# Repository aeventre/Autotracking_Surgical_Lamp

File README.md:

# AutoTracking Surgical Robot lamp

## Table of Contents
- [AutoTracking Surgical Robot lamp](#autotracking-surgical-robot-lamp)
  - [Table of Contents](#table-of-contents)
  - [Overview](#overview)
  - [Background](#background)
  - [Acknowledgments](#acknowledgments)
- [System Overview](#system-overview)
- [Software Design](#software-design)
  - [Setup](#setup)
  - [Package Overview](#package-overview)
    - [`command_manager`](#command_manager)
    - [`lamp_gui`](#lamp_gui)
    - [`remote_tracker`](#remote_tracker)
    - [`camera_calibration`](#camera_calibration)
    - [`goal_pose_executor`](#goal_pose_executor)
    - [`controller_coms`](#controller_coms)
    - [`surg_bot_description`](#surg_bot_description)
    - [`surg_bot_moveit_config`](#surg_bot_moveit_config)
  - [Launch Configurations](#launch-configurations)
- [Electrical Design](#electrical-design)
- [CAD](#cad)
  - [3D Printed Components of Surgical Robot](#3d-printed-components-of-surgical-robot)
  - [Sensors and Servos](#sensors-and-servos)
  - [Bill of materials for Surgical Robot](#bill-of-materials-for-surgical-robot)
  - [Bill of Materials for Surgical Robot Base](#bill-of-materials-for-surgical-robot-base)

## Overview
An open-source ROS 2 and MoveIt 2 surgical lamp capable of autonomous real-time tracking of a handheld remote using monocular vision and 3D pose estimation. 

## Background
This project aims to develop a solution to the challenges posed by modern surgical lamps,
particularly focused on the ceiling-mounted lamps. The proposed solution is a responsive
surgical lamp that uses real-time tracking and automated movement to adjust its lighting
position. This approach minimizes manual interaction, reduces delays and allows support staff
to remain focused on higher priority clinical responsibilities

# System Overview

# Software Design

This ROS 2 workspace contains all packages required for the Auto-Tracking Surgical Lamp system. The lamp uses 3D pose tracking of a handheld remote (via green ball detection) to plan and execute motions in real-time, with fallback modes for manual GUI control and demo sequences. The system is built using ROS 2 Jazzy and MoveIt 2.

## Setup

To build and source the workspace:

```bash
cd /path/to/ros2_ws
source /opt/ros/jazzy/setup.bash
rosdep install --from-paths src --ignore-src -r -y
colcon build
source install/setup.bash
```

## Package Overview

### `command_manager`

Manages the system's behavior based on user input. It switches between modes such as idle, manual control, tracking, zeroing, and demo.

**Subscriptions**
- `/system_mode` (`std_msgs/Int32`)
- `/remote_pose` (`geometry_msgs/PoseStamped`)
- `/remote_orientation` (`geometry_msgs/QuaternionStamped`)
- `/user_command` (`surg_lamp_msgs/UserCommand`)

**Publications**
- `/goal_pose` (`geometry_msgs/PoseStamped`)
- `/joint_commands` (`std_msgs/Float64MultiArray`)
- `/user_command` (`surg_lamp_msgs/UserCommand`)

---

### `lamp_gui`

PyQt5-based graphical user interface for interacting with the lamp.

**Features**
- Dropdown menu for system mode selection
- Sliders for manual joint control
- Buttons for triggering demo modes or resets
- Status label for system feedback

**Publications**
- `/system_mode` (`std_msgs/Int32`)
- `/joint_commands` (`std_msgs/Float64MultiArray`)
- `/user_command` (`surg_lamp_msgs/UserCommand`)

---

### `remote_tracker`

Tracks a green marker (ball) on a handheld remote using OpenCV and depth cameras. Estimates the 3D position and uses IMU orientation to compute the full pose.

**Inputs**
- RGB and depth images from stereo cameras
- Camera extrinsics from `camera_calibration`
- IMU orientation from the remote

**Outputs**
- `/remote_pose` (`geometry_msgs/PoseStamped`)
- `/remote_orientation` (`geometry_msgs/QuaternionStamped`)

---

### `camera_calibration`

Contains stereo camera calibration and extrinsic transform files.

**Contents**
- `camera_01.yaml`, `camera_02.yaml`: intrinsics for each camera
- `camera_01_to_base.yaml`, `camera_02_to_base.yaml`: transformations from camera to robot base frame

Used by the `remote_tracker` for accurate triangulation and transformation into the base frame.

---

### `goal_pose_executor`

Plans and executes motions from the current pose to the goal pose using MoveIt 2.

**Inputs**
- `/goal_pose` (`geometry_msgs/PoseStamped`)

**Behavior**
- Uses `MoveGroupInterface` to plan paths
- Sends joint angles to `/joint_commands`
- Reports failure if planning is unsuccessful

---

### `controller_coms`

Handles RS-485 serial communication with two microcontrollers that control the lamp's motors and lighting.

**Responsibilities**
- Sends joint angle commands to MCU1 and MCU2
- Receives and parses motor feedback
- Manages half-duplex communication (send then receive)
- Relays light mode and button state

**Serial Protocol**
- `mcu1`: `<joint1,joint2,joint3,joint4,lightmode>`
- `mcu2`: `<joint0>`
- Half-duplex format: send commands, then wait for and parse response

---

### `surg_bot_description`

URDF/Xacro model of the surgical lamp.

**Includes**
- Link and joint definitions
- Joint limits and axes
- Visual and collision meshes
- Base frame and end-effector frame definitions

Used for visualization and planning.

---

### `surg_bot_moveit_config`

MoveIt 2 configuration for the surgical lamp.

**Includes**
- Kinematics solvers
- OMPL planning pipeline
- SRDF and robot semantic info
- RViz and MoveGroup launch support

---

## Launch Configurations

```bash
# GUI
ros2 run lamp_gui lamp_gui

# Command manager
ros2 run command_manager command_manager

# Remote tracker
ros2 run remote_tracker remote_tracker_node

# Goal pose executor
ros2 run goal_pose_executor goal_pose_executor_node

# Controller communication
ros2 run controller_coms controller_coms_node
```

# Electrical Design

## Remote Design 

## PCB Design 

# Pictures

All links and joints links are avaiable to download in the CAD section as .STL and .SLDPRT

## 3D Printed Components of Surgical Robot
ABS was the material used to print the prototype. ABS and PETG would be good options to use as well

## Sensors and Servos 
Below is a list of sensors and motors being used 
- 160 KG Servos 
- 20 KG Servos
- Adafruit 9-DOF Orientation IMU Fusion Sensor
- Magnetic Encoder 
- NEMA 17
- Bluetooth/WiFi module
- Motor Drivers
- Orbbec 335 Cameras 

## Bill of materials for Surgical Robot
- Full HD webcam
- 4 channels IIC I2C logic level converter
- ESP32 Cam
- RS-485 MAX485 Transceiver
- 160 KG Servo
- Nema 17 Stepper
- Taidacent 12 wire 5A Slip Rings 
- USB to RS-485 Converter
- AS5600 Magnetic Encoder 
- Magnets 
- Laser Diodes
- LED Circle Array
- Raspberry Pi 5 8GB

## Bill of Materials for Surgical Robot Base

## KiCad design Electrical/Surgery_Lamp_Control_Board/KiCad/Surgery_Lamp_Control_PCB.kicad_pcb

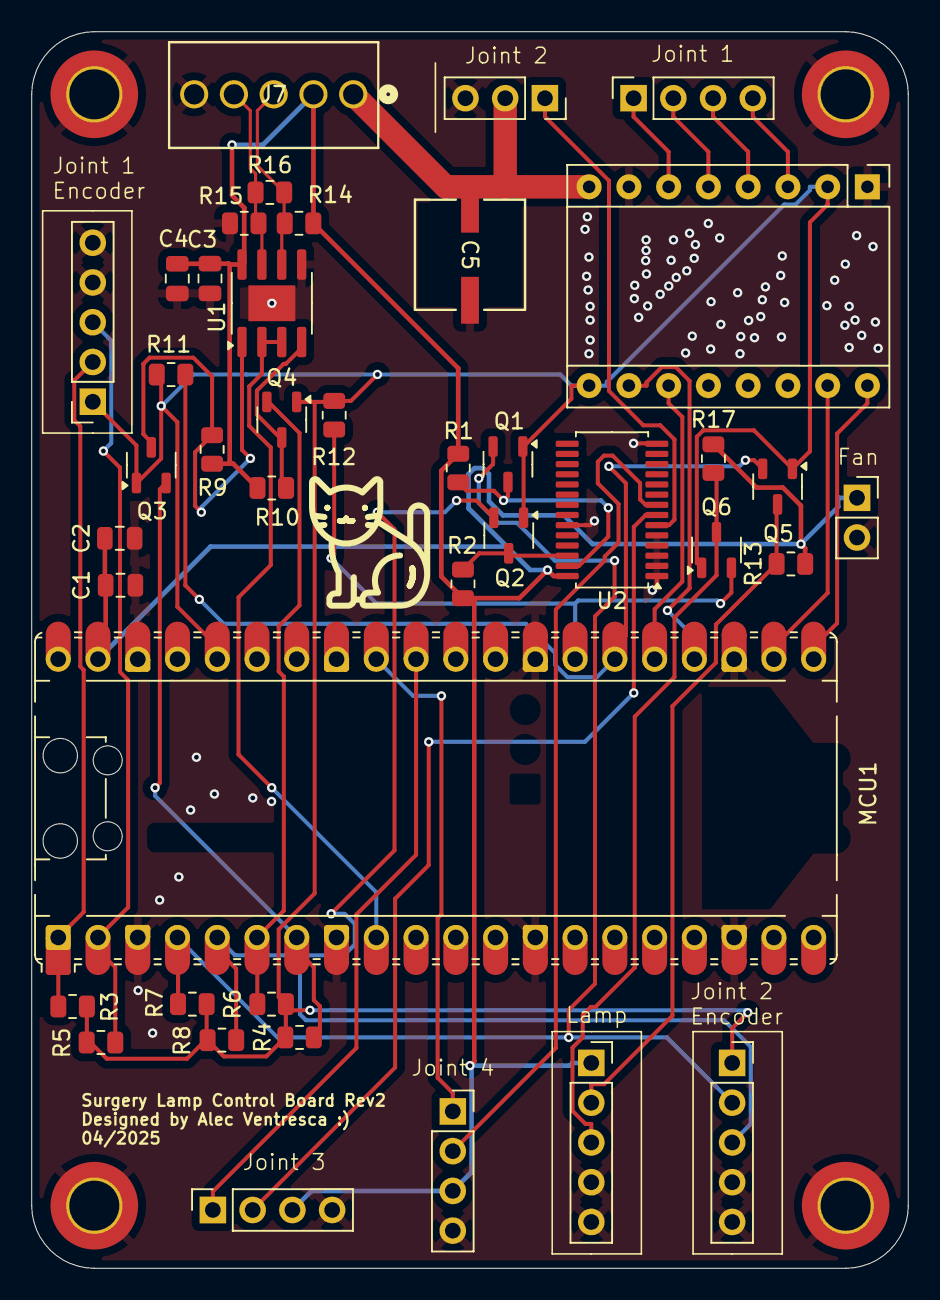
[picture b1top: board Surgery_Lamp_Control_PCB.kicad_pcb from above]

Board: 2 copper layers, 56.0 x 79.0 mm, 45 parts (0 on the bottom side), 34 nets.

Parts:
A1: TMC2209 Stepper Driver; Pololu_Breakout-16_15.2x20.3mm
C1, C3: 10uF; C_0805_2012Metric
C2, C4: 0.1uF; C_0805_2012Metric
C5: 47uF; CAP_6.3 X 5.8_PAN
H1, H2, H3, H4: MountingHole_Pad; MountingHole_3.2mm_M3_DIN965_Pad_TopBottom
J1: joint2; PinSocket_1x03_P2.54mm_Vertical
J2: joint3; PinSocket_1x04_P2.54mm_Vertical
J3: joint4; PinSocket_1x04_P2.54mm_Vertical
J4: Headlamp; PinSocket_1x05_P2.54mm_Vertical
J5: Joint 1 Encoder; PinSocket_1x05_P2.54mm_Vertical
J6: Joint 2 Encoder; PinSocket_1x05_P2.54mm_Vertical
J7: OSTVN05A150; CONN5_516x256_OST
J8: Stepper; PinSocket_1x04_P2.54mm_Vertical
J9: Fan; PinSocket_1x02_P2.54mm_Vertical
MCU1: RaspberryPi_Pico; RaspberryPi_Pico_Common_Unspecified
Q1, Q2, Q3, Q4, Q5, Q6: BSS138; SOT-23-3
R1, R2, R3, R4, R5, R6, R7, R8, R9, R10, R11, R12, R13, R17: 10k; R_0805_2012Metric
R14, R15: 20k; R_0805_2012Metric
R16: 120; R_0805_2012Metric
U1: MAX485E; SOIC-8-1EP_3.9x4.9mm_P1.27mm_EP2.29x3mm
U2: PCA9685PW; TSSOP-28_4.4x9.7mm_P0.65mm

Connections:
3V3: A1.2 (VIO), A1.9 (EN), J5.1, J6.1, MCU1.36 (3V3), Q1.1 (G), Q2.1 (G), Q3.1 (G), Q4.1 (G), Q5.1 (G), Q6.1 (G), R3.1, R4.1, R5.1, R6.1, R7.1, R8.1, R11.1, R12.1
5V: C1.1, C2.1, C3.1, C4.1, J2.3, J3.3, J4.1, J7.2, J9.1, MCU1.39 (VSYS), R1.1, R2.1, R9.1, R10.1, R13.1, R14.1, R17.1, U1.8 (VCC), U2.28 (VDD)
24V: A1.8 (VMOT), C5.1, J1.2, J7.1
DIR: A1.16 (DIR), MCU1.21 (GPIO16)
GND: A1.1 (GND), A1.7 (GND), C1.2, C2.2, C3.2, C4.2, C5.2, H1.1, H2.1, H3.1, H4.1, J1.3, J2.4, J3.4, J4.4, J4.5, J5.4, J5.5, J6.4, J6.5, J7.5, J9.2, MCU1.3 (GND), MCU1.8 (GND), MCU1.13 (GND), MCU1.18 (GND), MCU1.23 (GND), MCU1.28 (GND), MCU1.38 (GND), R15.2, U1.5 (GND), U1.9, U2.1 (A0), U2.2 (A1), U2.3 (A2), U2.4 (A3), U2.5 (A4), U2.14 (VSS), U2.23 (*OE)
MS1: A1.10 (MS1), MCU1.24 (GPIO18)
MS2: A1.11 (MS2), MCU1.25 (GPIO19)
unnamed: A1.5 (1A), J8.2
unnamed: A1.6 (1B), J8.1
unnamed: A1.4 (2A), J8.3
unnamed: A1.3 (2B), J8.4
unnamed: J1.1, U2.6 (LED0)
unnamed: J2.2, U2.7 (LED1)
unnamed: J3.2, U2.8 (LED2)
unnamed: MCU1.26 (GPIO20), Q5.2 (S), R11.2
unnamed: MCU1.27 (GPIO21), Q6.2 (S), R12.2
unnamed: Q3.3 (D), R9.2, U1.1 (RO)
unnamed: Q4.3 (D), R10.2, U1.4 (DI)
RS+: J7.3, R14.2, R16.1, U1.6 (A)
RS-: J7.4, R15.1, R16.2, U1.7 (B)
RS_Enable: MCU1.9 (GPIO6), U1.2 (~RE), U1.3 (DE)
RX: MCU1.7 (GPIO5), Q3.2 (S), R4.2
SCL0: J5.3, MCU1.2 (GPIO1), R5.2
SCL1: J6.3, MCU1.5 (GPIO3), Q2.2 (S), R8.2
SCL1_5V: Q2.3 (D), R2.2, U2.26 (SCL)
SDA0: J5.2, MCU1.1 (GPIO0), R3.2
SDA1: J6.2, MCU1.4 (GPIO2), Q1.2 (S), R7.2
SDA1_5V: Q1.3 (D), R1.2, U2.27 (SDA)
STEP: A1.15 (STEP), MCU1.22 (GPIO17)
TX: MCU1.6 (GPIO4), Q4.2 (S), R6.2
joint3_Feedback: J2.1, MCU1.31 (GPIO26_ADC0)
joint4_Feedback: J3.1, MCU1.32 (GPIO27_ADC1)
laser_pointer: J4.3, Q6.3 (D), R17.2
neopixel: J4.2, Q5.3 (D), R13.2

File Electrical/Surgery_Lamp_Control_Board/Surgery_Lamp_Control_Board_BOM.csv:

"Reference","Qty","Value","Footprint","Digikey Part Number"
"R1,R2,R3,R4,R5,R6,R7,R8,R9,R10,R11,R12,R13,R16,R17","15","10k","Resistor_SMD:R_0805_2012Metric","YAG2132CT-ND"
"J1","1","OSTVN05A150","Alec_lib:CONN5_516x256_OST","ED10564-ND"
"Q1,Q2,Q3,Q4,Q5,Q6","6","BSS138","Package_TO_SOT_SMD:SOT-23-3","BSS138-FDICT-ND"
"U2","1","PCA9685PW","Package_SO:TSSOP-28_4.4x9.7mm_P0.65mm","568-8366-5-ND"
"U1","1","MAX485E","Package_SO:SOIC-8-1EP_3.9x4.9mm_P1.27mm_EP2.29x3mm","4518-MAX485ESACT-ND"
"C1,C3","2","10uF","Capacitor_SMD:C_0805_2012Metric","399-C0805C106K4PACTUCT-ND"
"C2,C4","2","0.1uF","Capacitor_SMD:C_0805_2012Metric","399-C0805C104M5UACTUCT-ND"
"C5","1","47uF","Alec_lib:CAP_6.3 X 5.8_PAN","399-18135-1-ND"
"MCU1","1","RaspberryPi_Pico","Module:RaspberryPi_Pico_Common_Unspecified","2648-SC0915CT-ND"
"R14,R15","2","20k","Resistor_SMD:R_0805_2012Metric","13-RC0805FR-1020KLCT-ND"
"J8","1","Stepper","Connector_PinSocket_2.54mm:PinSocket_1x04_P2.54mm_Vertical",""
"J7","1","joint4","Connector_PinSocket_2.54mm:PinSocket_1x04_P2.54mm_Vertical",""
"J6","1","joint3","Connector_PinSocket_2.54mm:PinSocket_1x04_P2.54mm_Vertical",""
"J5","1","joint2","Connector_PinSocket_2.54mm:PinSocket_1x03_P2.54mm_Vertical",""
"J4","1","Joint 2 Encoder","Connector_PinSocket_2.54mm:PinSocket_1x05_P2.54mm_Vertical",""
"J3","1","Joint 1 Encoder","Connector_PinSocket_2.54mm:PinSocket_1x05_P2.54mm_Vertical",""
"J2","1","Headlamp","Connector_PinSocket_2.54mm:PinSocket_1x05_P2.54mm_Vertical",""
"H1,H2,H3,H4","4","MountingHole_Pad","MountingHole:MountingHole_3.2mm_M3_DIN965_Pad_TopBottom",""
"A1","1","Pololu_Breakout_DRV8825","Module:Pololu_Breakout-16_15.2x20.3mm",""

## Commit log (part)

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2024-10-05 Added packages to put the CAD into a sim
2024-10-07 Added URDF file for modeling the robot arm
2024-10-07 Added hand_tracker package for Zack's code
2024-10-07 Added SRC folder to hand_tracker
2024-10-14 Properly registered ROS2 packages
2024-10-25 Added gitignore
2024-10-25 emove build, install, and log folders from repository"
2024-10-25 Remove Source, build and log files from packages
2024-10-25 Deleted Even more unnecessary files
2024-10-25 I'm just moving everythin around
2024-10-31 Added python package for the hand tracking algorithm
2024-11-06 Created parameter file to enable gazebo to talk to ros2 topics
2024-11-07 I did a lot of stuff, but the URDF should be chill
2024-11-14 The URDF is like actually good, like joint states and everything
2024-11-16 Testing
2024-11-17 Changed naming to underscore standards :(
2024-11-17 Changed naming conventions
2024-11-17 updated CMakeLists
2024-11-17 Created necessary packages for simulation, all empty rn
2024-11-17 Fixed dependency typo
2024-11-17 Created empty.world
2024-11-17 Meshes are working in RVIZ but URDF needs to be completely reworked
2024-11-17 The URDF is like actually finally perfect for realsies this time
2024-11-18 Got RVIZ launch file to work fully, should be good to start integrating with gazebo next
2024-11-25 Update README.md
    making it FANCY
2024-11-27 nothing changed
2025-02-25 Add README for command manager package
2025-02-26 create serial_coms package
2025-02-26 add boilerplate code to serial_coms node
2025-02-26 update gitignore
2025-02-26 Add surg_bot_description package with URDF models and configuration files
2025-02-26 Add surg_bot_description package with initial configuration and remove obsolete files
2025-02-27 Add kinect_interface package with initial implementation and configuration files
2025-02-27 Remove obsolete meshes, configuration files, and documentation from surg_bot_description package
2025-02-27 Refactor HandTrackerNode to use serial communication instead of HTTP for image capture
2025-02-27 Add initial project structure with configuration files and README documentation
2025-02-27 Refactor HandTrackerNode to use webcam for hand tracking and remove serial communication
2025-02-27 Add inverse kinematics solver node for 2D robotic arm
2025-02-27 Add entry point for 2D inverse kinematics node
2025-02-27 Rename package from 2d_kinematics to kinematics_2d in setup.py
2025-02-27 Update package.xml and setup.cfg to reflect package name change to kinematics_2d; remove obsolete files and enhance test initialization.
2025-02-27 Remove kinect_interface package and associated files
2025-02-27 Refactor kinect_interface CMakeLists.txt to improve dependency management and specify library paths directly
2025-02-27 Add initial implementation of serial_coms package for sending joint angles to microcontroller
2025-02-27 Add launch file for planar motion, integrating IK solver and serial communication nodes
2025-02-27 Add data_files entry to setup.py for launch file installation
2025-02-27 Update planar motion launch file with correct package and executable names
2025-02-27 Add usage instructions to planar motion launch file
2025-03-19 Add README.md
2025-03-19 Add surg_lamp_msgs package with custom message definitions for surgical lamp project
2025-03-19 Add ControllerComsNode for serial communication with MCUs
2025-03-19 Remove unnecessary blank line in coms_node.py
2025-03-19 Add pyserial to requirements.txt for serial communication support
2025-03-19 Add pyyaml to requirements.txt for YAML support
2025-03-19 Update schematic files and .gitignore for improved organization
2025-03-19 Add initial project structure with .gitignore and README files for firmware, libraries, and tests
2025-03-22 Add initial implementation of surgBotLib library files
2025-03-22 Refactor project structure: consolidate .gitignore files, remove obsolete files, and add main.cpp for mcu1
2025-03-22 Refactor encoderLib integration and update platformio configuration for mcu1 and mcu2
2025-03-22 Remove obsolete README file and add unit tests for AS5600Interpolator class
2025-03-23 Update .gitignore to exclude PlatformIO build files
2025-03-23 Refactor moveit_planner package to use Python-based setup and dependencies
2025-03-23 Initial Structure for planner node
2025-03-23 Refactor AS5600Interpolator class: streamline initialization, improve angle reading, and enhance motor control logic
2025-03-23 Refactor encoderLib: replace AS5600Interpolator with EncoderLib, enhancing angle reading and motor control logic
2025-03-25 Update platformio configuration and implement main logic for mcu2 with servo control and command reception
2025-03-25 Update main logic in mcu2 to send current joint positions to ROS
2025-03-25 Refactor main logic in mcu2: improve code readability and formatting in setup and loop functions
2025-03-25 Update com ports
2025-03-25 Remove serial_coms package and update .gitignore to exclude PlatformIO files
2025-03-25 Add LampCurrentAngles message definition to surg_lamp_msgs
2025-03-25 Enhance ControllerComsNode with current angles publishing and improved MCU status checks
2025-03-27 Replace AS5600 encoder with EncoderLib: update setup and loop functions for improved angle readings
2025-03-27 Add .pio/ to .gitignore for improved file management
2025-04-02 Remove obsolete files and add .gitignore for Surgery Lamp Control Board
2025-04-02 Add .gitignore for Surgery Lamp Control Board and remove obsolete files
2025-04-03 Migrate moveit_planner package from Python to C++ implementation and update dependencies
2025-04-03 Implement moveit_planner_node in C++ and add launch file for execution
2025-04-03 Add camera_estimation_2d package with hand position publisher and configuration files
2025-04-03 Update .ini to include mcu3 environment
2025-04-03 Refactor hand position publisher to convert pixel coordinates to meters; improve logging and visualization
2025-04-03 mcu4 is the Receiver esp32 using the esp32now protocol and gather data from mcu3. The 3 different methods of interpreting the data is based on real time feedback
2025-04-03 Fix missing newline at end of file in hand position publisher
2025-04-06 Refactor mcu1 firmware to use DRV8834 driver and update library dependencies; add error check for text_on_edge_cuts in PCB design
2025-04-06 Add Adafruit BusIO library and ControllerLib; remove obsolete EncoderLib
2025-04-06 Add CommandParser and enhance ControllerLib for command handling and status reporting
2025-04-06 Add StepperJoint class for PID-controlled stepper motor management
2025-04-06 Refactor ControllerLib into Controller class; implement command handling and integrate servo and stepper management
2025-04-06 Add newline after status reporting in Controller update method for improved readability
2025-04-07 Refactor StepperJoint class; add encoder calibration method, improve angle calculations, and enhance PID control logic
2025-04-08 Refactor CommandParser and Controller; streamline initialization and update methods, enhance readability, and add test code for StepperJoint functionality in main.cpp
2025-04-08 Refactor ControllerComsNode to improve serial communication and remove threading; enhance MCU status reporting
2025-04-08 Refactor IK Solver to incorporate camera transform; enhance joint angle calculations and subscriptions for improved accuracy
2025-04-08 Add launch file for IK tracking; include nodes for hand position publishing and IK solver
2025-04-08 Refactor CommandParser for improved command handling and add RS485 control; clean up KiCad files
2025-04-08 It works!!!! As long as an encoder is attached
2025-04-09 Refactor EncoderLib integration and streamline main control logic; remove unused Servo dependencies
2025-04-10 Update platform configuration for mcu2 and clean up KiCad files; remove unused autosave and lock files
2025-04-11 Update MCU1 port configuration and adjust IK solver parameters for improved accuracy
2025-04-13 Update Surgery Lamp Control PCB files
2025-04-13 Remove lamp_1 mesh and update URDF references to link5_1 and end_effector_1
2025-04-13 Remove obsolete mesh files and update URDF references for improved model accuracy
2025-04-13 Change description to fix base origin
2025-04-13 Add initial implementation of goal_pose_computer package with setup and test files
2025-04-15 Add goal pose calculator node and launch configuration
2025-04-15 Remove unused test files and ignore type for tf_transformations import
2025-04-15 Fix direction calculation in GoalPoseNode for correct pose orientation
2025-04-16 Update joint velocity limits in configuration for improved safety
2025-04-16 Refactor joint names to lowercase and update related configurations for consistency
2025-04-17 Got all the IK working, just need to do the execution
2025-04-17 Refactor communication node to use Float64MultiArray for joint commands and add user command subscription; improve error handling for insufficient joint command values.
2025-04-18 Remove goal_pose_executor launch file as part of project cleanup
2025-04-19 Initial package create for command manager
2025-04-19 Update coms_node to act as joint state publisher
2025-04-22 Add pose input to GUI
2025-04-22 It Works!!!!!
2025-04-24 Update URDF to include apriltags
2025-04-25 Got the offset working with the IK
2025-04-25 Change motion planning algorithm to stomp from ompl
2025-04-25 Remove goal_pose_executor and kinematics_2d packages
    - Deleted the goal_pose_executor package, including its source files, package.xml, and CMakeLists.txt.
    - Removed the kinematics_2d package, including all source files, launch files, and configuration files.
    - Added a new camera_calibration package with initial setup, including package.xml, setup.py, and test files for copyright, flake8, and PEP257 compliance.
2025-04-26 Implement camera calibration node and launch configuration; remove obsolete test files
2025-04-26 Add launch files for spawning controllers and warehouse database
    - Created `spawn_controllers.launch.py` to facilitate the spawning of controllers for the `surg_bot` MoveIt configuration.
    - Created `warehouse_db.launch.py` to set up the warehouse database for the `surg_bot` MoveIt configuration.
    - Both launch files utilize the `MoveItConfigsBuilder` for configuration management.
2025-04-27 Add remote_tracker package with initial setup and calibration data updates
2025-04-27 Implement remote tracker node with camera synchronization and pose estimation
2025-04-28 Add NeoPixel to MCU
2025-04-29 Refactor controller and servo joint implementation; add light mode functionality and update main application logic
2025-04-29 Enhance ServoJoint functionality: add reversed attachment option, streamline angle setting, and update main application logic for joint2
2025-05-01 Add initial implementation of MarkerPoseEstimatorNode and launch configuration for ArUco tracking
2025-05-01 Refactor MarkerPoseEstimatorNode to improve parameter handling and add transformation mapping for detected markers; update launch file to align depth to color and adjust resolution settings.
2025-05-01 Tune all joint controllers
2025-05-01 Full system integration with launch file
2025-05-01 Update camera poses and enhance GUI functionality with improved shutdown handling and signal management
2025-05-01 Added two missing pins to mcu 2 code in mcu 1 branch
2025-05-03 change tuneing of PID on all motors and MCU1 now zeros at intial start. Also RS485 now wworks for MCU1 formated like <a1,a2,a3,a4,INT>
2025-05-04 RS-485 fix to send a recieve message when sent data
2025-05-04 Added wrist tracker package. Working out bugs in remote tracker. Fixed bugs in command manager
2025-05-04 Camera Calibration confirmed to be somewhat accurate
2025-05-05 Somewhat working. Values still very inaccurate.
2025-05-05 Add Neopixel with options that runs on RS485
2025-05-05 Increase tolerance for orientation allowing for less planning fails
2025-05-06 updated joint offset
2025-05-07 Implement demo mode with preset poses
2025-05-09 Add final prototype CAD for remote and arm
2025-05-09 Add remote control code
